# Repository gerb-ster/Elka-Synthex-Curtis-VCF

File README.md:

# Elka Synthex 'Curtis' VCF

A clone of the VCF found in the Elka Synthex around the CEM 3320 IC. This project is still 'work in progress', a
prototype has been build, but it's not quite bug free. 

_the current design needs to be debugged_

## Status: Work in Progress

- done: first schematic & board design
- done: breadboard and test
- done: design frontpanel
- done: order PCB 
- todo: build (working) prototype

## Links

https://bitbucket.org/XNOTOX/synthex-vcf/src/master/ 
https://electricdruid.net/cem3320-filter-designs/ 
https://www.instructables.com/How-to-Program-an-Attiny85-From-an-Arduino-Uno/

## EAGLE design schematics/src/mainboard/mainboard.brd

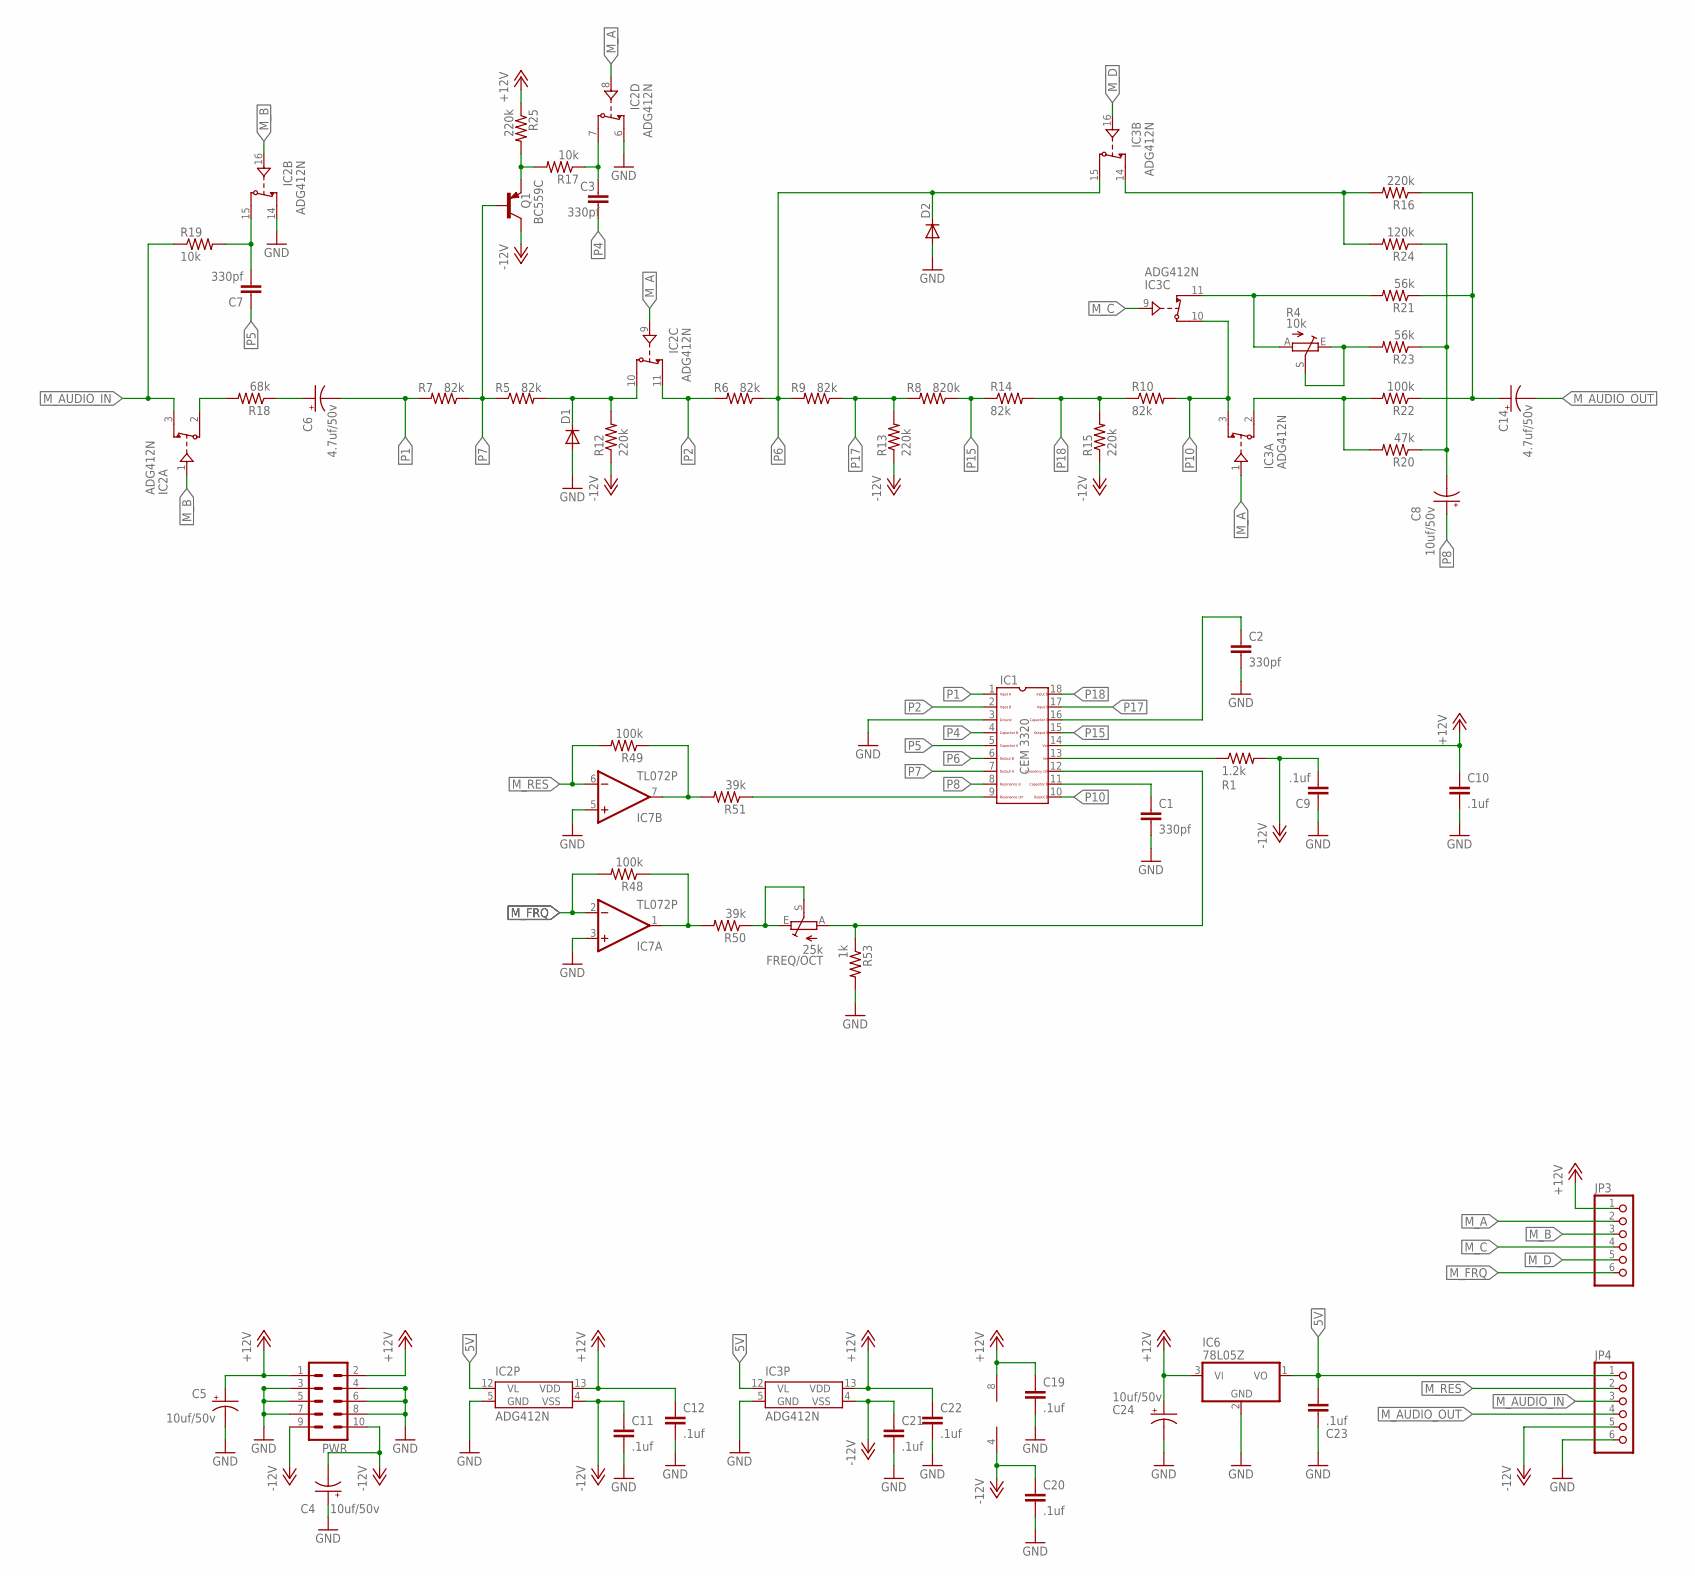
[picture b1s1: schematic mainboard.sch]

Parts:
C1, C2, C3, C7: 330pf; C050-050X075
C4, C5, C8, C24: 10uf/50v; E2,5-5
C6, C14: 4.7uf/50v; E2,5-5
C9, C10, C11, C12, C19, C20, C21, C22, C23: .1uf; C050-024X044
D1, D2: 1N4148DO35-7; DO35-7
FREQ/OCT: 25k; S64YW
IC1: CEM3320; DIL18
IC2, IC3: ADG412N; DIL16
IC6: 78L05Z; TO92
IC7: TL072P; DIL08
JP3, JP4: PINHD-1X6; 1X06
PWR: ML10
Q1: BC559C; TO92-EBC
R1: 1.2k; 0207/10
R4: 10k; S64YW
R5, R6, R7, R9, R10, R14: 82k; 0207/10
R8: 820k; 0207/10
R12, R13, R15, R16, R25: 220k; 0207/10
R17, R19: 10k; 0207/10
R18: 68k; 0207/10
R20: 47k; 0207/10
R21, R23: 56k; 0207/10
R22, R48, R49: 100k; 0207/10
R24: 120k; 0207/10
R50, R51: 39k; 0207/10
R53: 1k; 0207/10

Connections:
5V: C23.1, IC2.12 (VL), IC3.12 (VL), IC6.1 (VO), JP4.1
+12V: C5.+, C10.1, C12.1, C19.1, C22.1, C24.+, IC1.14, IC2.13 (VDD), IC3.13 (VDD), IC6.3 (VI), IC7.8 (V+), JP3.1, PWR.1, PWR.2, R25.1
-12V: C4.-, C9.2, C11.1, C20.1, C21.1, IC2.4 (VSS), IC3.4 (VSS), IC7.4 (V-), JP4.5, PWR.9, PWR.10, Q1.C, R1.2, R12.1, R13.1, R15.1
GND: C1.1, C2.2, C4.+, C5.-, C9.1, C10.2, C11.2, C12.2, C19.2, C20.2, C21.2, C22.2, C23.2, C24.-, D1.A, D2.A, IC1.3, IC2.5 (GND), IC2.6 (S), IC2.14 (S), IC3.5 (GND), IC6.2 (GND), IC7.3 (+IN), IC7.5 (+IN), JP4.6, PWR.3, PWR.4, PWR.5, PWR.6, PWR.7, PWR.8, R53.2
INT_FRQ: FREQ/OCT.A, IC1.12, R53.1
INT_RES: IC1.9, R51.1
M_A: IC2.8 (IN), IC2.9 (IN), IC3.1 (IN), JP3.2
M_AUDIO_IN: IC2.3 (S), JP4.3, R19.1
M_AUDIO_OUT: C14.-, JP4.4
M_B: IC2.1 (IN), IC2.16 (IN), JP3.3
M_C: IC3.9 (IN), JP3.4
M_D: IC3.16 (IN), JP3.5
M_FRQ: IC7.2 (-IN), JP3.6, R48.2
M_RES: IC7.6 (-IN), JP4.2, R49.2
unnamed: Q1.E, R17.2, R25.2
unnamed: C6.+, R18.1
unnamed: D1.C, IC2.10 (D), R5.2, R12.2
unnamed: IC3.2 (D), R20.2, R22.2
unnamed: IC2.2 (D), R18.2
unnamed: C7.2, IC2.15 (D), R19.2
unnamed: R4.E, R4.S, R23.2
unnamed: C3.1, IC2.7 (D), R17.1
unnamed: C14.+, R16.1, R21.1, R22.1
unnamed: IC3.11 (S), R4.A, R21.2
unnamed: IC3.14 (S), R16.2, R24.2
unnamed: C8.-, R20.1, R23.1, R24.1
unnamed: C2.1, IC1.16
unnamed: IC1.13, R1.1
unnamed: C1.2, IC1.11
unnamed: FREQ/OCT.E, FREQ/OCT.S, R50.1
unnamed: IC7.7 (OUT), R49.1, R51.2
unnamed: IC7.1 (OUT), R48.1, R50.2
P1: C6.-, IC1.1, R7.2
P2: IC1.2, IC2.11 (S), R6.2
P4: C3.2, IC1.4
P5: C7.1, IC1.5
P6: D2.C, IC1.6, IC3.15 (D), R6.1, R9.2
P7: IC1.7, Q1.B, R5.1, R7.1
P8: C8.+, IC1.8
P10: IC1.10, IC3.3 (S), IC3.10 (D), R10.2
P15: IC1.15, R8.1, R14.1
P17: IC1.17, R8.2, R9.1, R13.2
P18: IC1.18, R10.1, R14.2, R15.2

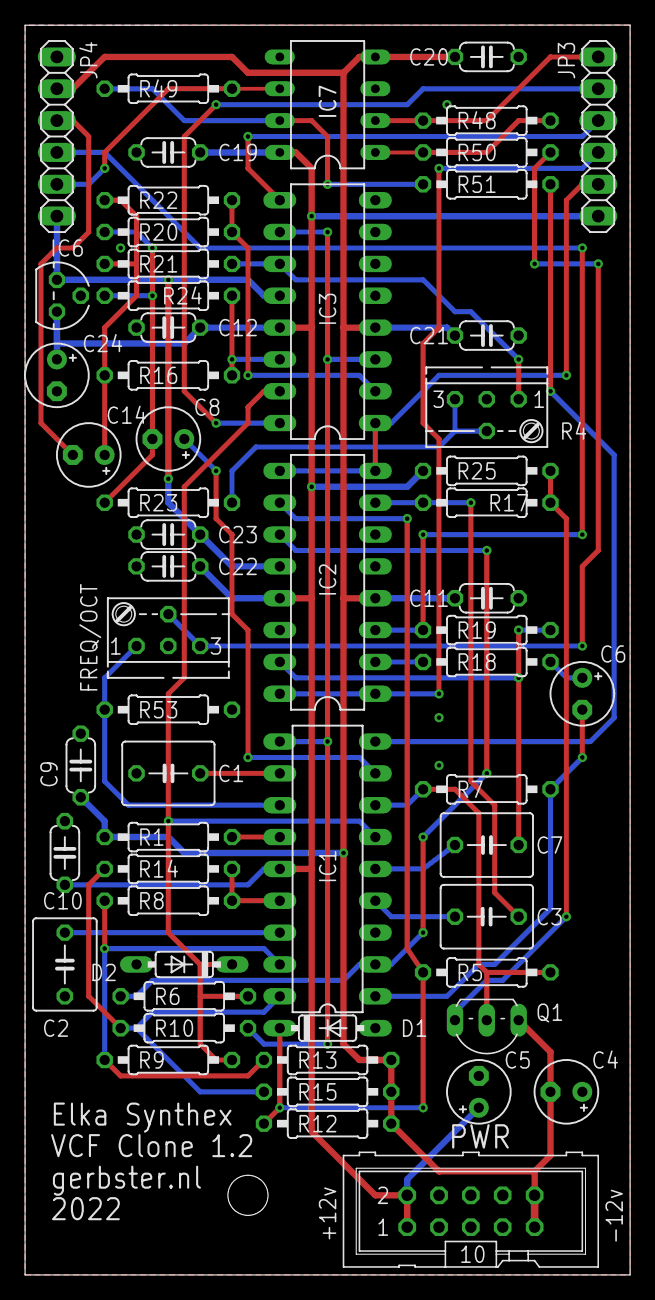
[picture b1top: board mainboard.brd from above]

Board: 2 copper layers, 48.3 x 99.7 mm, 58 parts (0 on the bottom side), 43 nets.

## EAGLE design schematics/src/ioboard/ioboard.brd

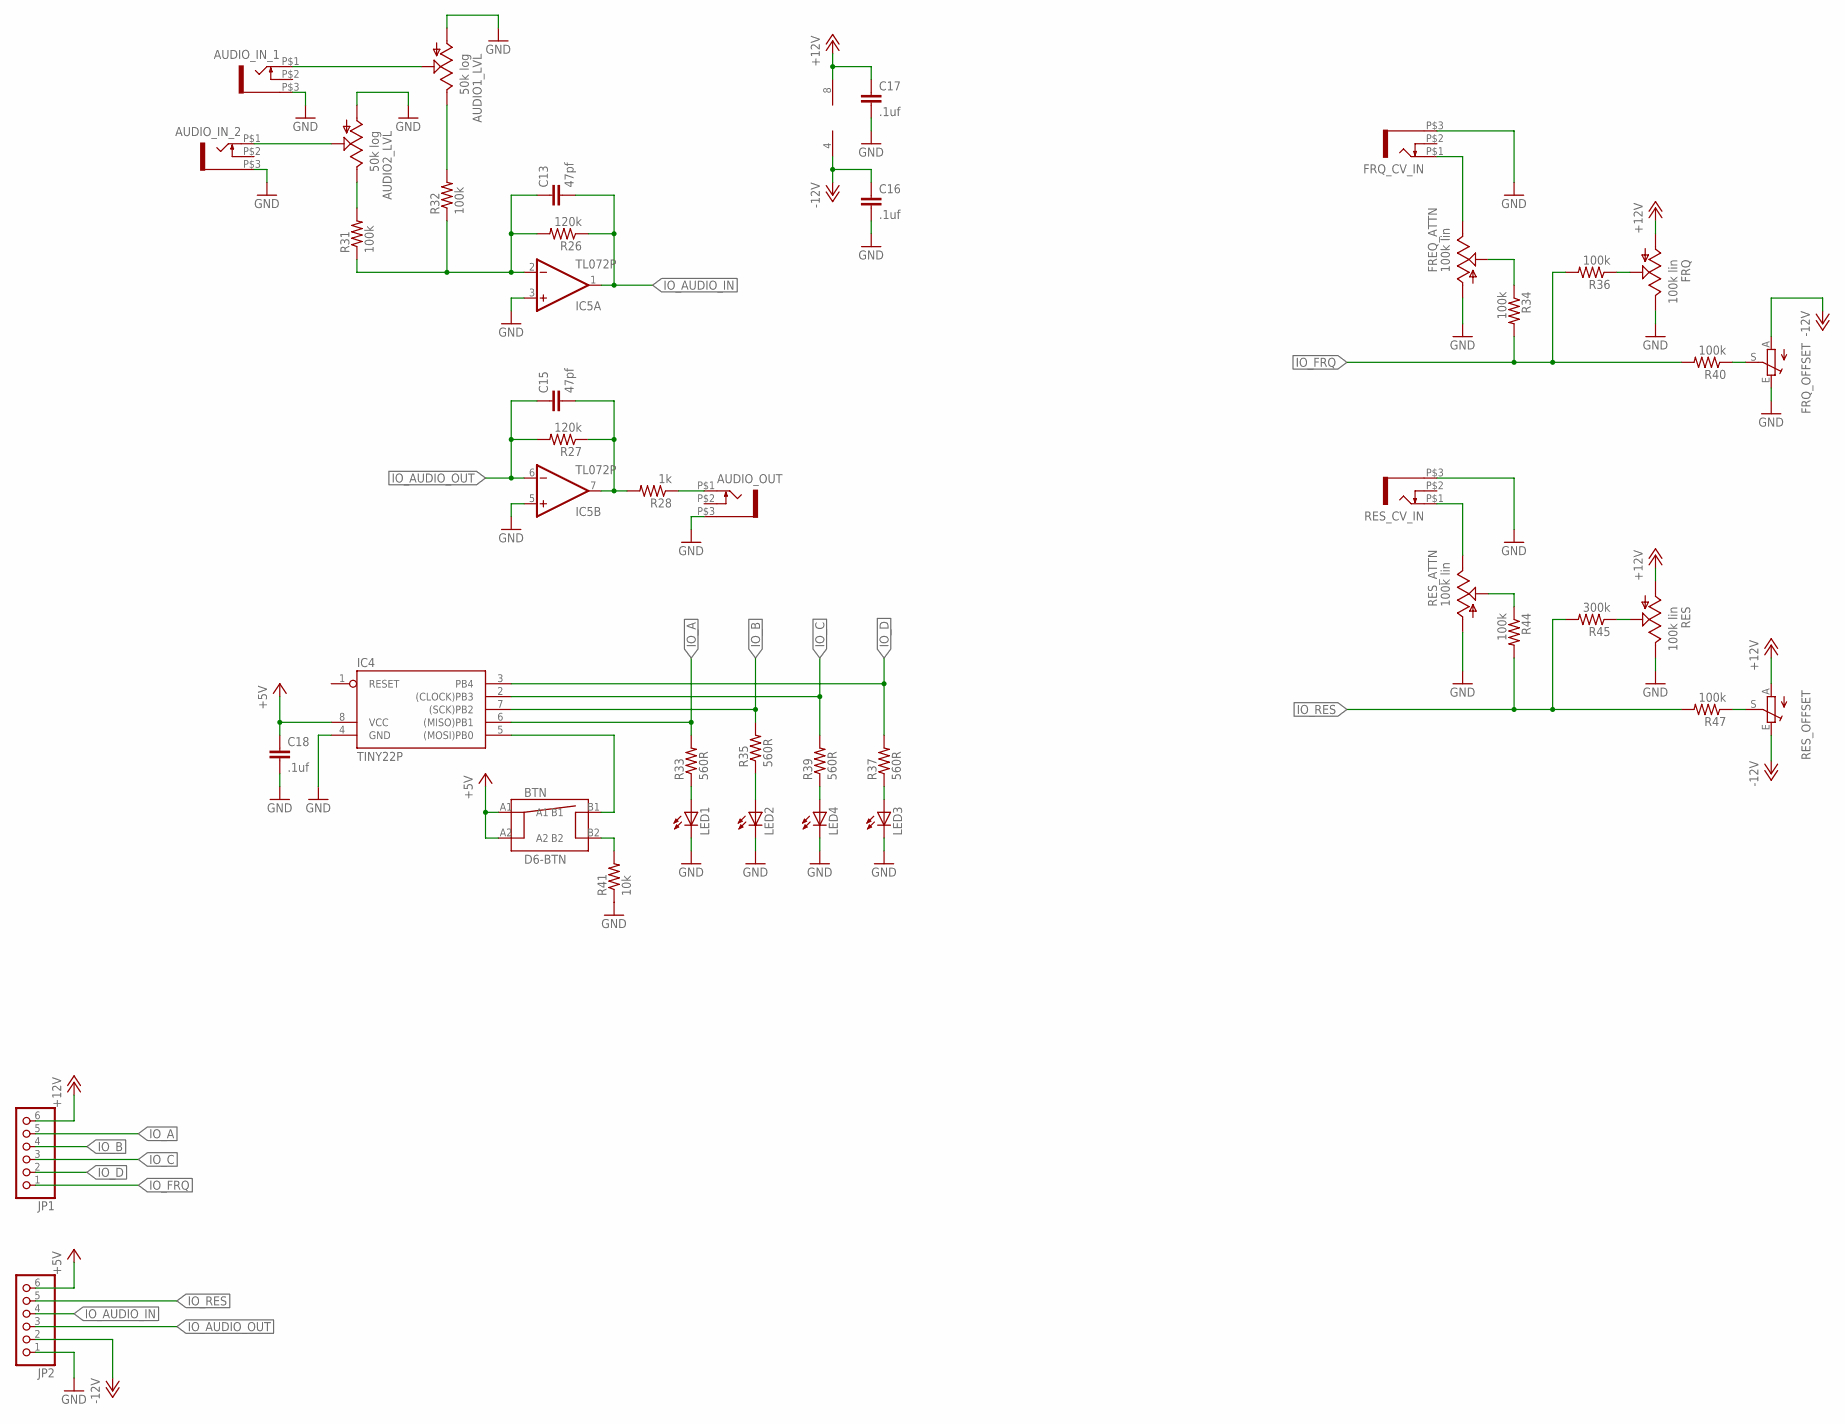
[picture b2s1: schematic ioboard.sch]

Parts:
AUDIO1_LVL, AUDIO2_LVL: 50k log; EVUF
AUDIO_IN_1, AUDIO_IN_2: WQP-PJ301M-12_JACK
AUDIO_OUT: WQP-PJ301M-12_JACK
BTN: D6-BTN
C13, C15: 47pf; C050-024X044
C16, C17, C18: .1uf; C050-024X044
FREQ_ATTN: 100k lin; EVUF
FRQ: 100k lin; EVUF
FRQ_CV_IN: WQP-PJ301M-12_JACK
FRQ_OFFSET: TRIM_EU-B25P; B25P
IC4: TINY22P; DIL08
IC5: TL072P; DIL08
JP1, JP2: PINHD-1X6; 1X06
LED1, LED2, LED3, LED4: LED3MM
R26, R27: 120k; 0207/7
R28: 1k; 0207/7
R31, R32, R34, R36, R40, R44, R47: 100k; 0207/7
R33, R35, R37, R39: 560R; 0207/7
R41: 10k; 0207/7
R45: 300k; 0207/7
RES: 100k lin; EVUF
RES_ATTN: 100k lin; EVUF
RES_CV_IN: WQP-PJ301M-12_JACK
RES_OFFSET: TRIM_EU-B25P; B25P

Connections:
+5V: BTN.A1, BTN.A2, C18.1, IC4.8 (VCC), JP2.6
+12V: C17.1, FRQ.1 (A), IC5.8 (V+), JP1.6, RES.1 (A), RES_OFFSET.A
-12V: C16.1, FRQ_OFFSET.A, IC5.4 (V-), JP2.2, RES_OFFSET.E
GND: AUDIO1_LVL.1 (A), AUDIO2_LVL.1 (A), AUDIO_IN_1.P$3 (1), AUDIO_IN_2.P$3 (1), AUDIO_OUT.P$3 (1), C16.2, C17.2, C18.2, FREQ_ATTN.1 (A), FRQ.3 (E), FRQ_CV_IN.P$3 (1), FRQ_OFFSET.E, IC4.4 (GND), IC5.3 (+IN), IC5.5 (+IN), JP2.1, LED1.K (C), LED2.K (C), LED3.K (C), LED4.K (C), R41.1, RES.3 (E), RES_ATTN.1 (A), RES_CV_IN.P$3 (1)
IO_A: IC4.6 ((MISO)PB1), JP1.5, R33.2
IO_AUDIO_IN: C13.2, IC5.1 (OUT), JP2.4, R26.1
IO_AUDIO_OUT: C15.1, IC5.6 (-IN), JP2.3, R27.2
IO_B: IC4.7 ((SCK)PB2), JP1.4, R35.2
IO_C: IC4.2 ((CLOCK)PB3), JP1.3, R39.2
IO_D: IC4.3 (PB4), JP1.2, R37.2
IO_FRQ: JP1.1, R34.2, R36.2, R40.2
IO_RES: JP2.5, R44.2, R45.2, R47.2
unnamed: AUDIO_OUT.P$1 (2), R28.1
unnamed: C15.2, IC5.7 (OUT), R27.1, R28.2
unnamed: C13.1, IC5.2 (-IN), R26.2, R31.1, R32.1
unnamed: AUDIO2_LVL.3 (E), R31.2
unnamed: AUDIO1_LVL.3 (E), R32.2
unnamed: AUDIO2_LVL.2 (S), AUDIO_IN_2.P$1 (2)
unnamed: AUDIO1_LVL.2 (S), AUDIO_IN_1.P$1 (2)
unnamed: LED1.A, R33.1
unnamed: FREQ_ATTN.3 (E), FRQ_CV_IN.P$1 (2)
unnamed: FREQ_ATTN.2 (S), R34.1
unnamed: FRQ.2 (S), R36.1
unnamed: FRQ_OFFSET.S, R40.1
unnamed: LED2.A, R35.1
unnamed: RES_ATTN.3 (E), RES_CV_IN.P$1 (2)
unnamed: LED4.A, R39.1
unnamed: BTN.B2, R41.2
unnamed: BTN.B1, IC4.5 ((MOSI)PB0)
unnamed: R44.1, RES_ATTN.2 (S)
unnamed: R45.1, RES.2 (S)
unnamed: LED3.A, R37.1
unnamed: R47.1, RES_OFFSET.S

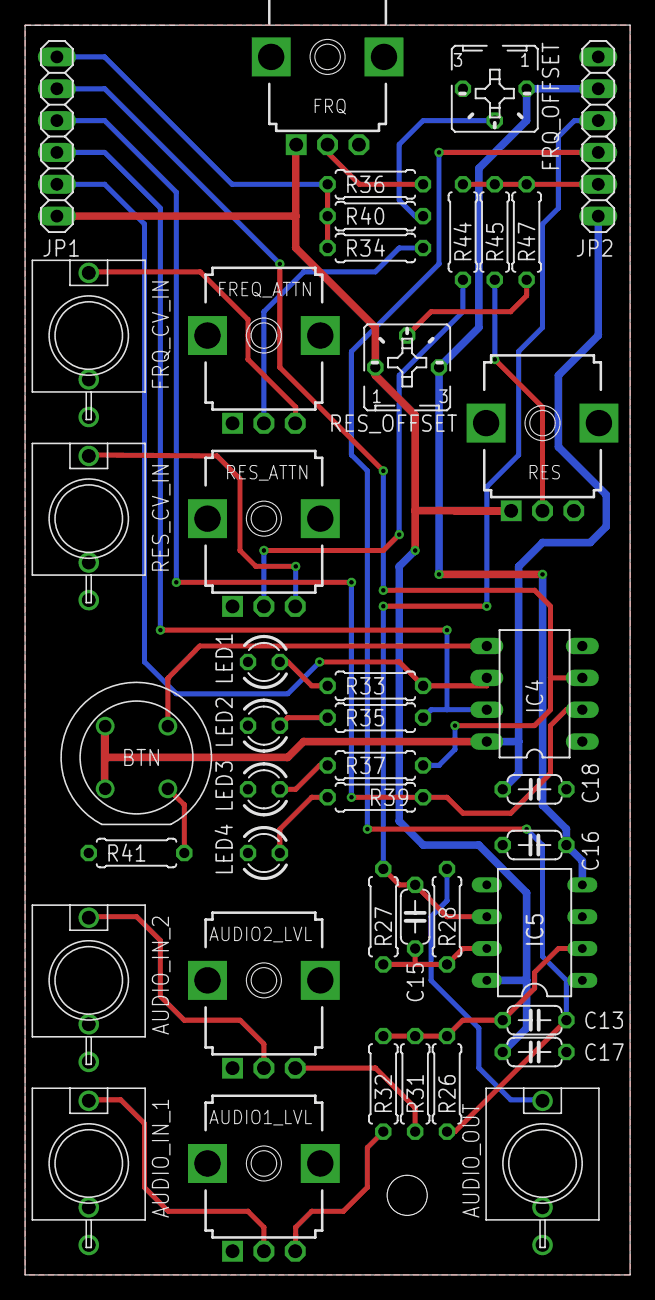
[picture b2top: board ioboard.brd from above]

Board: 2 copper layers, 48.3 x 99.7 mm, 43 parts (0 on the bottom side), 33 nets.

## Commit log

2021-05-10 Added files & structure
2021-05-10 added disclaimer
2021-05-11 Added Status & Images
2021-08-06 Updated some schematics and docs
2021-08-10 Fixed some bugs and updated documentation
2022-04-20 Some updates & bugfixes
2022-04-22 Fixed schematics & descriptions
2022-05-17 Updated Firmware
2022-05-18 Updated Faceplates
2022-05-18 Fixed issues
2022-05-21 Fixed schematics
2022-05-28 General updates
2022-06-26 Faceplates & Bugfixes
